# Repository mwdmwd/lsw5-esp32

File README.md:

# lsw5-esp32

> ESP32-based replacement PCB for the Deye/Sofar/Igen/Solarman/... LSW-5 *Stick Logger* with RS-485 CT meter emulation

This is a replacement ESP32-S3 daughterboard for the "LSW-5" *Stick Logger* (FCC ID [2A4FRLSW-5](https://fccid.io/2A4FRLSW-5)).

It replaces the original board, which is based on a [Hi-Flying HF-LPT270](http://www.hi-flying.com/hf-lpt270) [^lpt270] ([BL602](https://en.bouffalolab.com/product/?type=detail&id=1) inside[^lpt270-why-not]). With an ESP32-S3, it enables ESPHome support while keeping the *Stick Logger*'s modern, minimalistic appearance intact[^rs485-hole].

## Compatibility

* **Target Device**: LSW-5 *Stick Logger*, FCC ID: [2A4FRLSW-5](https://fccid.io/2A4FRLSW-5) and others (for example, mine, which does not have an FCC ID printed on it). May also fit the [2BC8DLSW-5](https://fccid.io/2BC8DLSW-5) (not verified, no internal photos), or other types of *Stick Logger*.
  * If your *Stick Logger* looks similar to the FCC photos, this board may fit regardless of whether the inverter-side connector is USB, DB-9, or the round 4-pin type.
* **Connection**: This board replaces the internal daughterboard connected via two (2x3, 2x5) socketed 2 mm pin headers.

## Features

* **ESP32-S3** (WROOM-1U-N16R8) with WiFi, BLE and a USB-C port for flashing/debugging.
* Works with **ESPHome**.
* 2.54 mm **expansion header** with 4 GPIOs with no predetermined function. Add a temperature sensor, I²C display, or any peripheral supported by ESPHome (or any other software you choose to run).
* **Open source hardware** designed in KiCad.
* Isolated **RS-485** transceiver for meter emulation.
  * Requires external 5V supply, as available from the *Meter-485* port in (some?) Deye hybrid inverters. Or use a phone charger to power it.[^rs485-isolation]
  * One isolated RS-485 port is present, but it could *potentially* be used for both meter emulation and BMS communication by connecting those to the same bus and configuring addresses appropriately; the Deye DSP firmware is hardcoded to use `1` for the "external CT" meter and `2` for the "Grid Tie Meter2" so these addresses are not available for BMS use. Unsure about address `0`.
    * You could definitely choose to use it *only* for BMS communication, with projects like [esphome-jk-bms](https://github.com/syssi/esphome-jk-bms)
* **LEDs**: on-board status LEDs (NET, RDY, COM) matching the translucent windows in the stock case mapped to ESP32 GPIOs.

## Hardware

The design files (schematics and PCB layout) are available in this repository.

### Pinout

| Function                               | ESP32 pin         | Location                      | Remarks                                                                     |
| :------------------------------------- | :---------------- | :---------------------------- | :-------------------------------------------------------------------------- |
| **3.3V input** from carrier board      | `3V3`             | J4 pins 5, 6                  |                                                                             |
| **GND** from carrier board             | `GND`             | J1 pins 1, 2, 3; J4 pins 9, 10 |                                                                             |
|                                        |                   |                               |                                                                             |
| **RX from inverter** (RS232 [^rs232])  | `GPIO16`          | J4 pin 8                      |                                                                             |
| **TX to inverter** (RS232)             | `GPIO17`          | J4 pin 7                      |                                                                             |
| **RX from RS485**                      | `GPIO21`          | onboard                       |                                                                             |
| **TX to RS485**                        | `GPIO48`          | onboard                       |                                                                             |
| **DE to RS485**                        | `GPIO47`          | onboard                       |                                                                             |
|                                        |                   |                               |                                                                             |
| **ESP32 boot mode**                    | `GPIO0`           | J1 pin 4                      | Connected to GND by the momentary switch on the bottom of the carrier board |
| **RX(?) from SIM card slot**           | `GPIO5`           | J4 pin 1                      | Slot is not populated on the carrier board, can use as GPIO                 |
| **TX(?) from SIM card slot**           | `GPIO4`           | J4 pin 4                      | Slot is not populated on the carrier board, can use as GPIO                 |
|                                        |                   |                               |                                                                             |
| **NET** LED                            | `GPIO40`          | onboard                       | Active low                                                                  |
| **COM** LED                            | `GPIO38`          | onboard                       | Active low                                                                  |
| **RDY** LED                            | `GPIO39`          | onboard                       | Active low                                                                  |
|                                        |                   |                               |                                                                             |
| **Programming port**[^usbc] 3.3V input | `3V3`             | J2 pin 1                      |                                                                             |
| **TX to external UART programmer**     | `TXD0` / `GPIO43` | J2 pin 2                      | Mind the startup messages                                                   |
| **RX from external UART programmer**   | `RXD0` / `GPIO44` | J2 pin 3                      |                                                                             |
| **GND**                                | `GND`             | J2 pin 4                      |                                                                             |
|                                        |                   |                               |                                                                             |
| **Expansion port:** 3.3V               | `3V3`             | J_EXP1 pin 1                  |                                                                             |
| Unassigned                             | `GPIO9`           | J_EXP1 pin 2                  |                                                                             |
| Unassigned                             | `GPIO10`          | J_EXP1 pin 3                  |                                                                             |
| Unassigned                             | `GPIO11`          | J_EXP1 pin 4                  |                                                                             |
| Unassigned                             | `GPIO12`          | J_EXP1 pin 5                  |                                                                             |
| GND                                    | `GND`             | J_EXP1 pin 6                  |                                                                             |
|                                        |                   |                               |                                                                             |
| **5V input** for RS485 transceiver     |                   | J6 pin 1                      |                                                                             |
| **GND** for RS485 transceiver          |                   | J6 pin 2                      |                                                                             |
| RS485 **A/+**                          |                   | J6 pin 3                      |                                                                             |
| RS485 **B/-**                          |                   | J6 pin 4                      |                                                                             |

There are two connections to the inverter:

- `GPIO16`/`GPIO17` connect to the inverter's MCU1/HMI through the logger port using the logger carrier's RS232 transceiver.
- `GPIO21`/`GPIO48`/`GPIO47` drive this board's RS485 transceiver and connect to the inverter's separate Meter-485 port, which is handled directly by MCU2/DSP.

## Errata

Board revisions refer to manufactured Gerber releases, tagged in Git as `p0`, `p1`, etc. The current KiCad files may already contain changes for the next unreleased revision; those changes are not listed here until a board is manufactured. For example, if the schematic says `p2` but there is no `p2` tag, that revision has not been manufactured yet.

Errata are listed by the newest affected revision. Older revisions also inherit the errata listed above them. For example, a `p0` board has both the `p1` and `p0` errata.

* `p1`
  * RS485 port: GND/5V labels swapped on silkscreen
  * Carrier board pin headers: silkscreen is on the wrong side
  * R5 should be 10 kΩ, not 100 kΩ
  * COM and NET LED labels swapped on silkscreen
  * LEDs are connected backwards compared to the intended design
  * RS485 bus interface includes series resistors, changed to 0 Ω at the moment, but either way they are not in a good place for proper termination (as the 120 Ω termination resistor is *after* the series resistor, not before), so they should probably be removed completely
* `p0`
  * No revision label on silkscreen
  * Non-isolated RS485 transceiver is used

## Firmware

[ESPHome](https://github.com/esphome/esphome), I suppose? This board is compatible with various existing ESPHome configurations (sometimes requiring minor adjustments).

* **[esphome-deye-inverter](https://github.com/Lewa-Reka/esphome-deye-inverter)**: A very comprehensive configuration for Deye inverters, including probably all of the sensors and switches you could ever want.
* **[esphome-for-deye](https://github.com/klatremis/esphome-for-deye)**: The classic.
* **[Sunsynk-Home-Assistant-Dash](https://github.com/slipx06/Sunsynk-Home-Assistant-Dash/tree/main/ESPHome%20Configs)**: You'll need to adjust the UART pins.
* *[your configuration here?]*

### Example configuration for board-specific features

A sample [`esphome/lsw5-esp32.yaml`](./esphome/lsw5-esp32.yaml) file is included in this repository. It serves as a starting point, illustrating the correct pin mappings for this specific board. It includes basic MQTT setup and RS-485 configuration for external meter emulation with source data over MQTT, as well as LED support.

> [!NOTE]
> The inverter polls the RS-485 meter every 125 ms, except every 10th attempt which is delayed by 125 ms as the inverter tries to write `float32(0.0)` to register 286 on device 0xab. I have not been able to identify the reason / meaning of this.
>
> You should aim to keep the data in your emulator as fresh as possible to minimize over/undershooting of the *Zero Export to Grid* feature under meter emulation.

## License

The hardware design files are licensed under the CERN Open Hardware Licence Version 2 - Strongly Reciprocal (CERN-OHL-S-2.0). See [LICENSES/CERN-OHL-S-2.0.txt](./LICENSES/CERN-OHL-S-2.0.txt) for details.

The example ESPHome configuration is based on an Apache-2.0-licensed configuration and has been modified for this project. It is distributed under the Apache License, Version 2.0. See [LICENSES/Apache-2.0.txt](./LICENSES/Apache-2.0.txt) and [esphome/NOTICE](./esphome/NOTICE) for details.

All other supporting files and tools are licensed under the GNU General Public License Version 3 or, at your option, any later version (GPL-3.0-or-later). See [LICENSES/GPL-3.0.txt](./LICENSES/GPL-3.0.txt) for details.

> [!CAUTION]
> Please be careful with electricity, always disconnect the *Stick Logger* from the inverter before replacing its internal board, always turn off the inverter and disconnect it from all power sources before (dis)connecting the *Stick Logger*, and so on. I will not be responsible if your warranty is voided, your inverter is damaged, or you get shocked. If you are not sure about something, ask for help from someone who is qualified to work with power electronics.

----------

[^lpt270]: https://fccid.io/2ACSVHF-LPT270-0F
[^rs485-hole]: unless you decide to cut a hole in the case to route out the Meter-485 cable. Or cut a bit of the plastic around the DB-9 plug out and route it there, but there is a risk of forgetting about the additional cable and causing damage when enthusiastically removing the *Stick Logger*. Or route it through the reset button hole.
[^rs485-isolation]: Added in `p1`, the story is that it would work fine until connecting the RS-485 (then all sorts of weird stuff would happen). I had seen some noise between the `GND`s in the RS-485 port and the RS-232 port, and the fact that they are not electrically connected, so I decided to make an isolated revision. Then it turned out that with 3cb155f6de7685bc65d782d9486902e5723dc495 my p0 board works on the bench, but isolation seems to be a good idea regardless.
[^rs232]: Through the RS232 transceiver on the carrier board inside the *Stick Logger* which this board plugs into.
[^usbc]: Recommended to use the USB-C port for programming instead
[^lpt270-why-not]: The ESP32-S3 was chosen because its software development experience and ESPHome support are substantially better.

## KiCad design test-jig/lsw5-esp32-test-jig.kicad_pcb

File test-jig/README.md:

# lsw5-esp32 test-jig

If you need this, you will know how to use it.

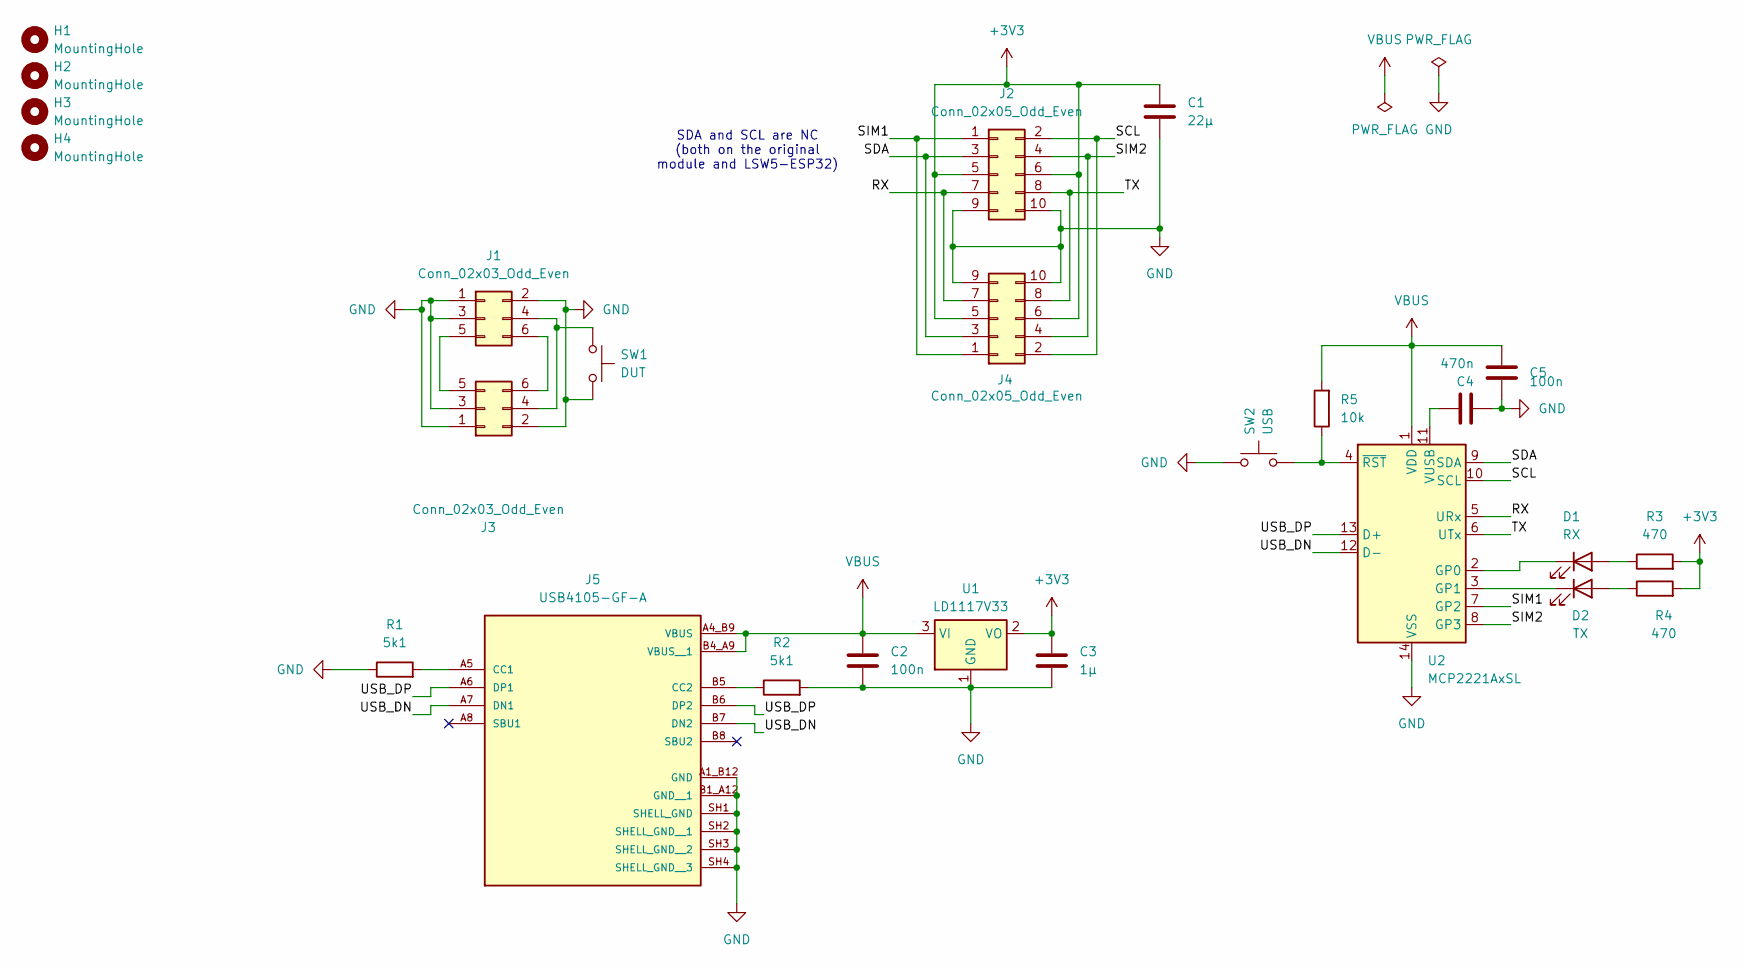
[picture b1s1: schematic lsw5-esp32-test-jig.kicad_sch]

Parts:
C1: 22μ; C_0805_2012Metric_Pad1.18x1.45mm_HandSolder
C2, C5: 100n; C_0603_1608Metric_Pad1.08x0.95mm_HandSolder
C3: 1μ; C_0603_1608Metric_Pad1.08x0.95mm_HandSolder
C4: 470n; C_0603_1608Metric_Pad1.08x0.95mm_HandSolder
D1: RX; LED_0603_1608Metric_Pad1.05x0.95mm_HandSolder
D2: TX; LED_0603_1608Metric_Pad1.05x0.95mm_HandSolder
H1, H2, H3, H4: MountingHole; MountingHole_3.2mm_M3
J1: Conn_02x03_Odd_Even; PinSocket_2x03_P2.00mm_Vertical
J2: Conn_02x05_Odd_Even; PinSocket_2x05_P2.00mm_Vertical
J3: Conn_02x03_Odd_Even; PinHeader_2x03_P2.54mm_Vertical
J4: Conn_02x05_Odd_Even; PinHeader_2x05_P2.54mm_Vertical
J5: USB4105-GF-A; GCT_USB4105-GF-A; PARTREV B4
R1, R2: 5k1; R_0603_1608Metric_Pad0.98x0.95mm_HandSolder
R3, R4: 470; R_0603_1608Metric_Pad0.98x0.95mm_HandSolder
R5: 10k; R_0603_1608Metric_Pad0.98x0.95mm_HandSolder
SW1: DUT; SW_PUSH_6mm
SW2: USB; SW_PUSH_6mm
U1: LD1117V33; TO-220-3_Vertical
U2: MCP2221AxSL; SOIC-14_3.9x8.7mm_P1.27mm

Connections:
+3V3: C1.1, C3.1, J2.5, J2.6, J4.5, J4.6, R3.2, R4.2, U1.2 (VO)
/RX: J2.7, J4.7, U2.5 (URx)
/SCL: J2.2, J4.2, U2.10 (SCL)
/SDA: J2.3, J4.3, U2.9 (SDA)
/SIM1: J2.1, J4.1, U2.7 (GP2)
/SIM2: J2.4, J4.4, U2.8 (GP3)
/TX: J2.8, J4.8, U2.6 (UTx)
/USB_DN: J5.A7 (DN1), J5.B7 (DN2), U2.12 (D-)
/USB_DP: J5.A6 (DP1), J5.B6 (DP2), U2.13 (D+)
GND: C1.2, C2.2, C3.2, C4.2, C5.2, J1.1, J1.2, J1.3, J2.9, J2.10, J3.1, J3.2, J3.3, J4.9, J4.10, J5.A1_B12 (GND), J5.B1_A12 (GND__1), J5.SH1 (SHELL_GND), J5.SH2 (SHELL_GND__1), J5.SH3 (SHELL_GND__2), J5.SH4 (SHELL_GND__3), R1.1, R2.2, SW1.2, SW2.1, U1.1 (GND), U2.14 (VSS)
unnamed: D1.2 (A), R3.1
unnamed: D1.1 (K), U2.2 (GP0)
unnamed: D2.2 (A), R4.1
unnamed: D2.1 (K), U2.3 (GP1)
unnamed: J1.4, J3.4, SW1.1
unnamed: J1.5, J3.5
unnamed: J1.6, J3.6
unnamed: J5.A5 (CC1), R1.2
unnamed: J5.B5 (CC2), R2.1
unnamed: C4.1, U2.11 (VUSB)
unnamed: R5.1, SW2.2, U2.4 (~RST)
VBUS: C2.1, C5.1, J5.A4_B9 (VBUS), J5.B4_A9 (VBUS__1), R5.2, U1.3 (VI), U2.1 (VDD)

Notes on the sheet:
SDA and SCL are NC (both on the original module and LSW5-ESP32)

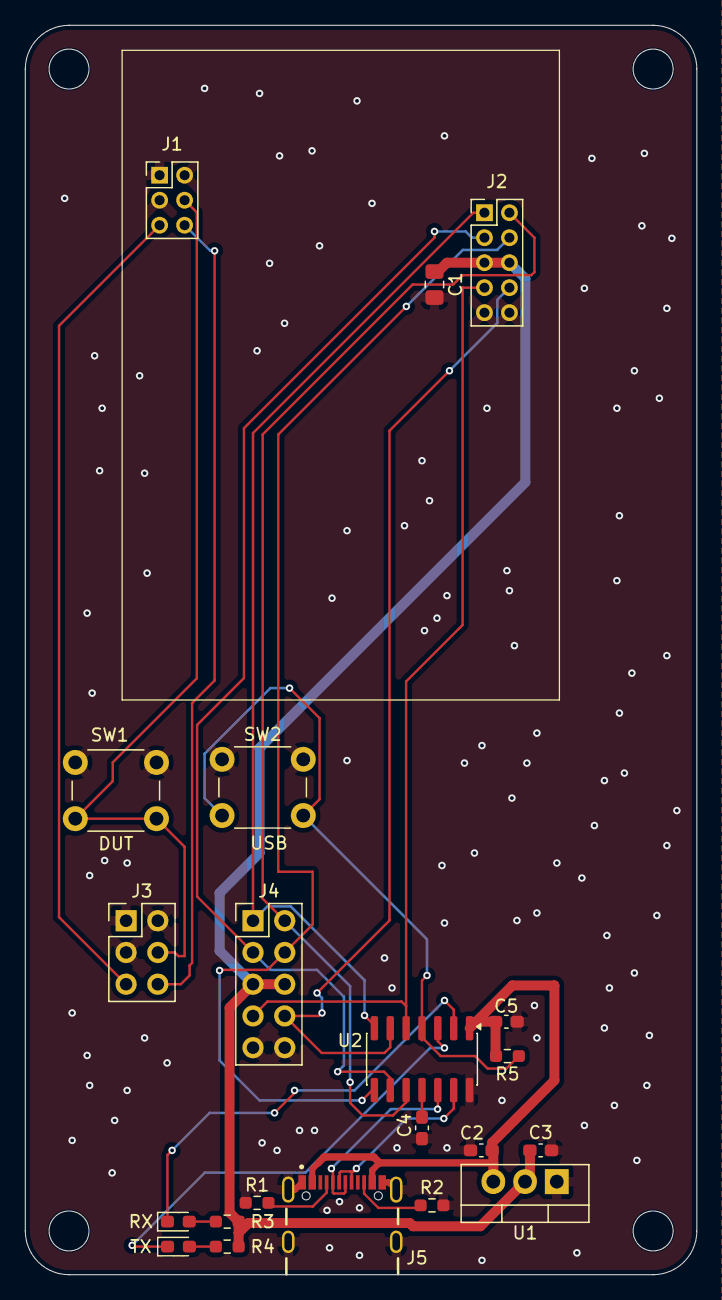
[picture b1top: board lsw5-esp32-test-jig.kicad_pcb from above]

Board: 2 copper layers, 53.8 x 100.0 mm, 25 parts (0 on the bottom side), 22 nets.

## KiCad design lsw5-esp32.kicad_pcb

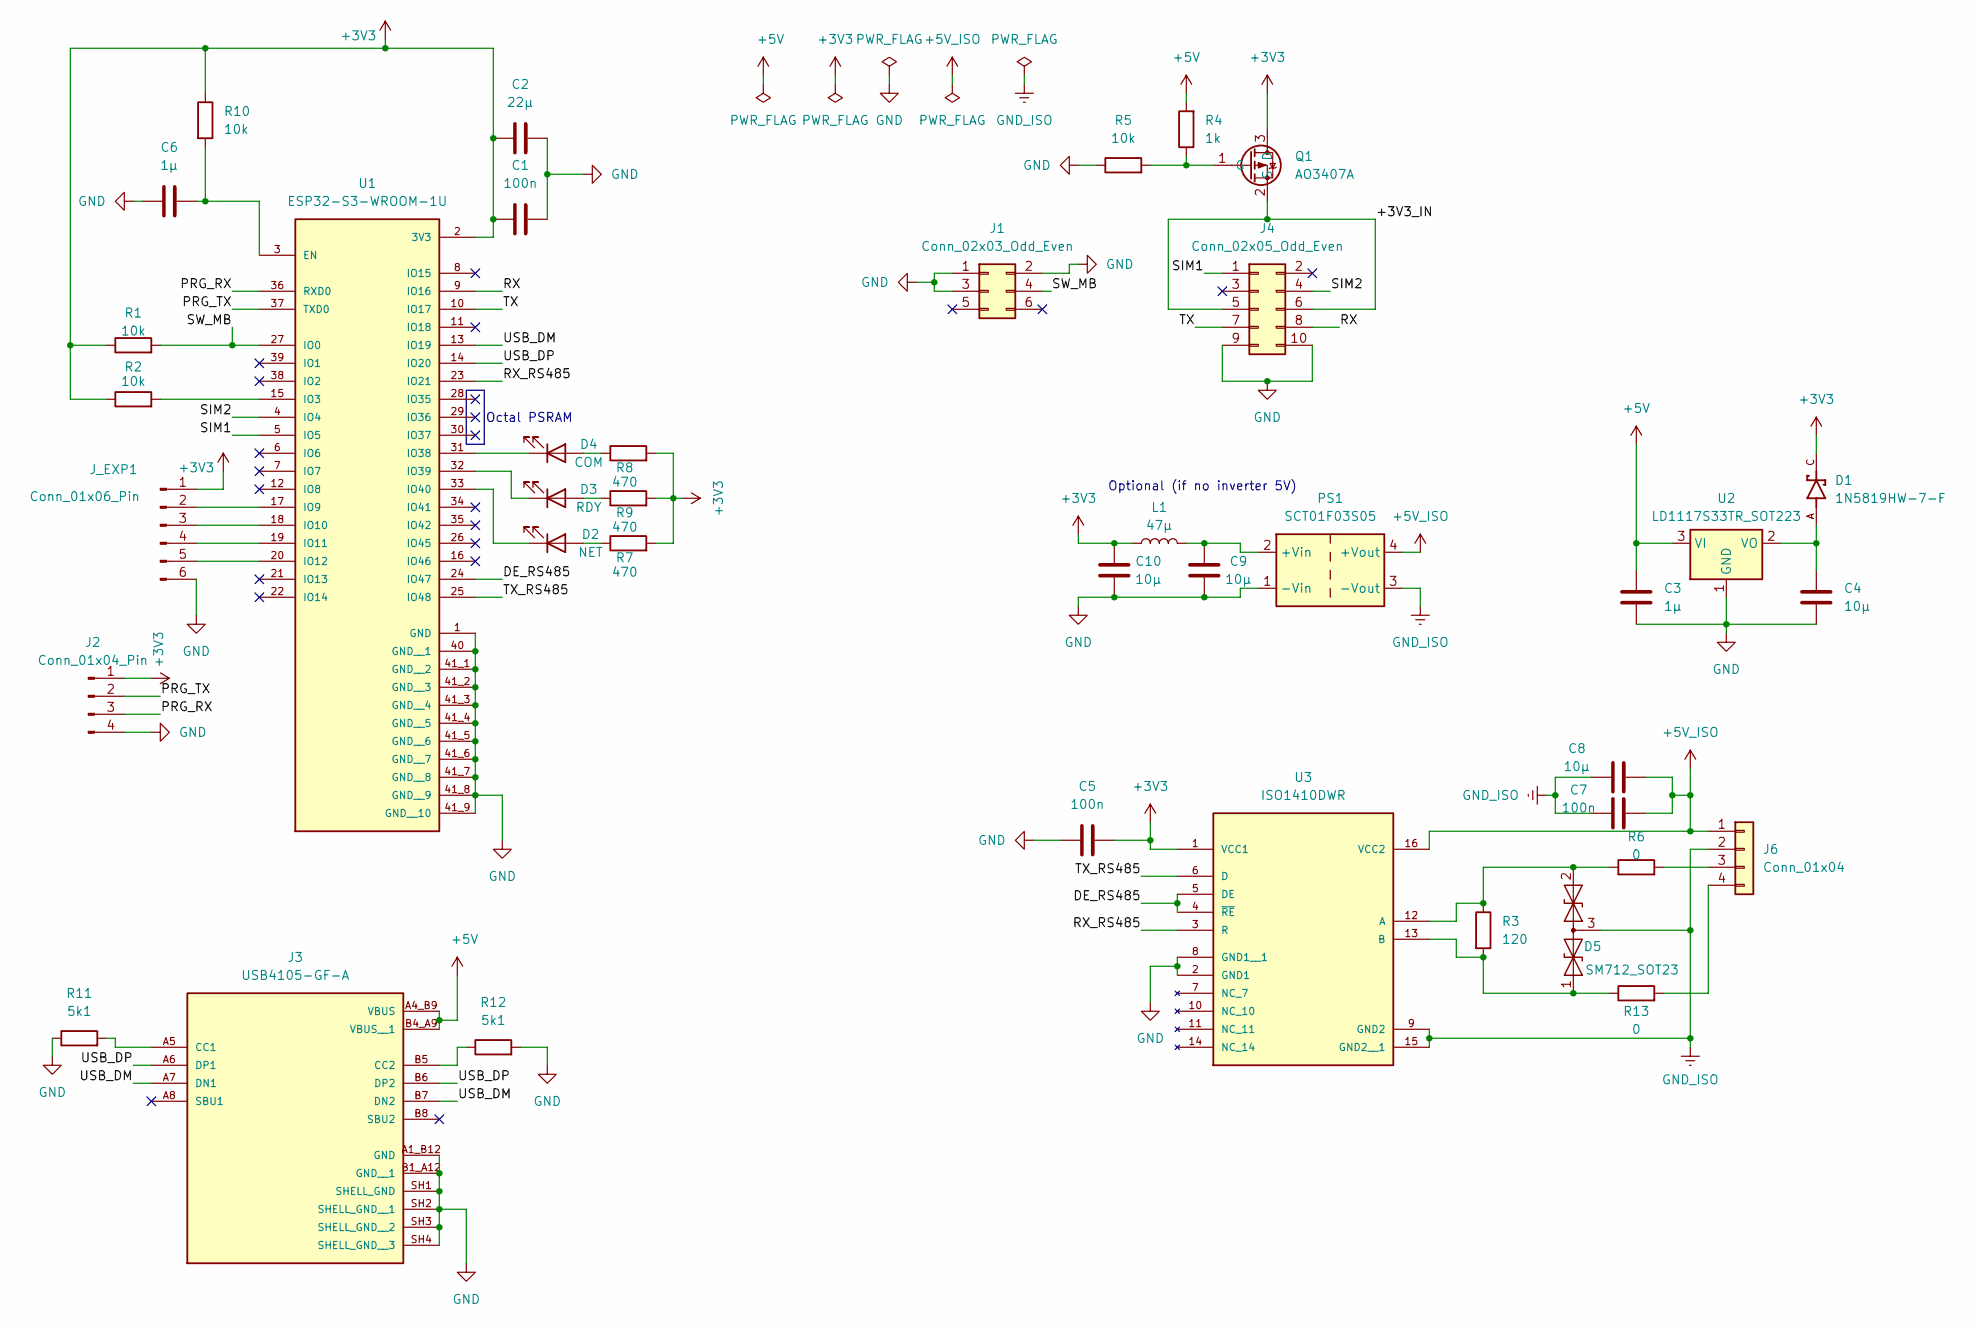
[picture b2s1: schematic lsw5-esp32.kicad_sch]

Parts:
C1, C5, C7: 100n; C_0603_1608Metric_Pad1.08x0.95mm_HandSolder
C2: 22μ; C_0805_2012Metric_Pad1.18x1.45mm_HandSolder
C3, C6: 1μ; C_0603_1608Metric_Pad1.08x0.95mm_HandSolder
C4, C8, C9, C10: 10μ; C_0805_2012Metric_Pad1.18x1.45mm_HandSolder
D1: 1N5819HW-7-F; SOD3715X145N; PARTREV 18-2
D2: NET; LED_0603_1608Metric_Pad1.05x0.95mm_HandSolder
D3: RDY; LED_0603_1608Metric_Pad1.05x0.95mm_HandSolder
D4: COM; LED_0603_1608Metric_Pad1.05x0.95mm_HandSolder
D5: SM712_SOT23; SOT-23
J1: Conn_02x03_Odd_Even; PinHeader_2x03_P2.00mm_Vertical
J2: Conn_01x04_Pin; PinHeader_1x04_P2.54mm_Vertical
J3: USB4105-GF-A; GCT_USB4105-GF-A; PARTREV B4
J4: Conn_02x05_Odd_Even; PinHeader_2x05_P2.00mm_Vertical
J6: Conn_01x04; PinHeader_1x04_P2.54mm_Vertical
J_EXP1: Conn_01x06_Pin; PinHeader_1x06_P2.54mm_Horizontal
L1: 47μ; L_Ferrocore_DJNR-4018
PS1: SCT01F03S05; Converter_DCDC_Murata_MEE1SxxxxSC_THT
Q1: AO3407A; SOT-23
R1, R2, R5, R10: 10k; R_0603_1608Metric_Pad0.98x0.95mm_HandSolder
R3: 120; R_0603_1608Metric_Pad0.98x0.95mm_HandSolder
R4: 1k; R_0603_1608Metric_Pad0.98x0.95mm_HandSolder
R6, R13: 0; R_0603_1608Metric_Pad0.98x0.95mm_HandSolder
R7, R8, R9: 470; R_0603_1608Metric_Pad0.98x0.95mm_HandSolder
R11, R12: 5k1; R_0603_1608Metric_Pad0.98x0.95mm_HandSolder
U1: ESP32-S3-WROOM-1U; ESP32-S3-WROOM-1U-N16R8; PARTREV v1.1
U2: LD1117S33TR_SOT223; SOT-223-3_TabPin2
U3: ISO1410DWR; SOIC127P1030X265-16N; PARTREV H

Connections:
+3V3: C1.1, C2.1, C5.1, C10.2, D1.C, J2.1, J_EXP1.1, L1.1, Q1.3 (D), R1.1, R2.1, R7.2, R8.2, R9.2, R10.1, U1.2 (3V3), U3.1 (VCC1)
+5V: C3.2, J3.A4_B9 (VBUS), J3.B4_A9 (VBUS__1), R4.2, U2.3 (VI)
+5V_ISO: C7.1, C8.1, J6.1, PS1.4 (+Vout), U3.16 (VCC2)
/+3V3_IN: J4.5, J4.6, Q1.2 (S)
/DE_RS485: U1.24 (IO47), U3.4 (~RE), U3.5 (DE)
/PRG_RX: J2.3, U1.36 (RXD0)
/PRG_TX: J2.2, U1.37 (TXD0)
/RX: J4.8, U1.9 (IO16)
/RX_RS485: U1.23 (IO21), U3.3 (R)
/SIM1: J4.1, U1.5 (IO5)
/SIM2: J4.4, U1.4 (IO4)
/SW_MB: J1.4, R1.2, U1.27 (IO0)
/TX: J4.7, U1.10 (IO17)
/TX_RS485: U1.25 (IO48), U3.6 (D)
/USB_DM: J3.A7 (DN1), J3.B7 (DN2), U1.13 (IO19)
/USB_DP: J3.A6 (DP1), J3.B6 (DP2), U1.14 (IO20)
GND: C1.2, C2.2, C3.1, C4.1, C5.2, C6.1, C9.1, C10.1, J1.1, J1.2, J1.3, J2.4, J3.A1_B12 (GND), J3.B1_A12 (GND__1), J3.SH1 (SHELL_GND), J3.SH2 (SHELL_GND__1), J3.SH3 (SHELL_GND__2), J3.SH4 (SHELL_GND__3), J4.9, J4.10, J_EXP1.6, PS1.1 (-Vin), R5.1, R11.1, R12.2, U1.1 (GND), U1.40 (GND__1), U1.41_1 (GND__2), U1.41_2 (GND__3), U1.41_3 (GND__4), U1.41_4 (GND__5), U1.41_5 (GND__6), U1.41_6 (GND__7), U1.41_7 (GND__8), U1.41_8 (GND__9), U1.41_9 (GND__10), U2.1 (GND), U3.2 (GND1), U3.8 (GND1__1)
GND_ISO: C7.2, C8.2, D5.3 (common), J6.2, PS1.3 (-Vout), U3.9 (GND2), U3.15 (GND2__1)
unnamed: C9.2, L1.2, PS1.2 (+Vin)
unnamed: D2.2 (A), R7.1
unnamed: D2.1 (K), U1.33 (IO40)
unnamed: D3.2 (A), R9.1
unnamed: D3.1 (K), U1.32 (IO39)
unnamed: D4.2 (A), R8.1
unnamed: D4.1 (K), U1.31 (IO38)
unnamed: D5.1 (A1), R3.2, R13.1, U3.13 (B)
unnamed: D5.2 (A2), R3.1, R6.1, U3.12 (A)
unnamed: J3.A5 (CC1), R11.2
unnamed: J3.B5 (CC2), R12.1
unnamed: J6.3, R6.2
unnamed: J6.4, R13.2
unnamed: J_EXP1.2, U1.17 (IO9)
unnamed: J_EXP1.3, U1.18 (IO10)
unnamed: J_EXP1.4, U1.19 (IO11)
unnamed: J_EXP1.5, U1.20 (IO12)
unnamed: Q1.1 (G), R4.1, R5.2
unnamed: C6.2, R10.2, U1.3 (EN)
unnamed: R2.2, U1.15 (IO3)
unnamed: C4.2, D1.A, U2.2 (VO)

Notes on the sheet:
Optional (if no inverter 5V)
Octal PSRAM

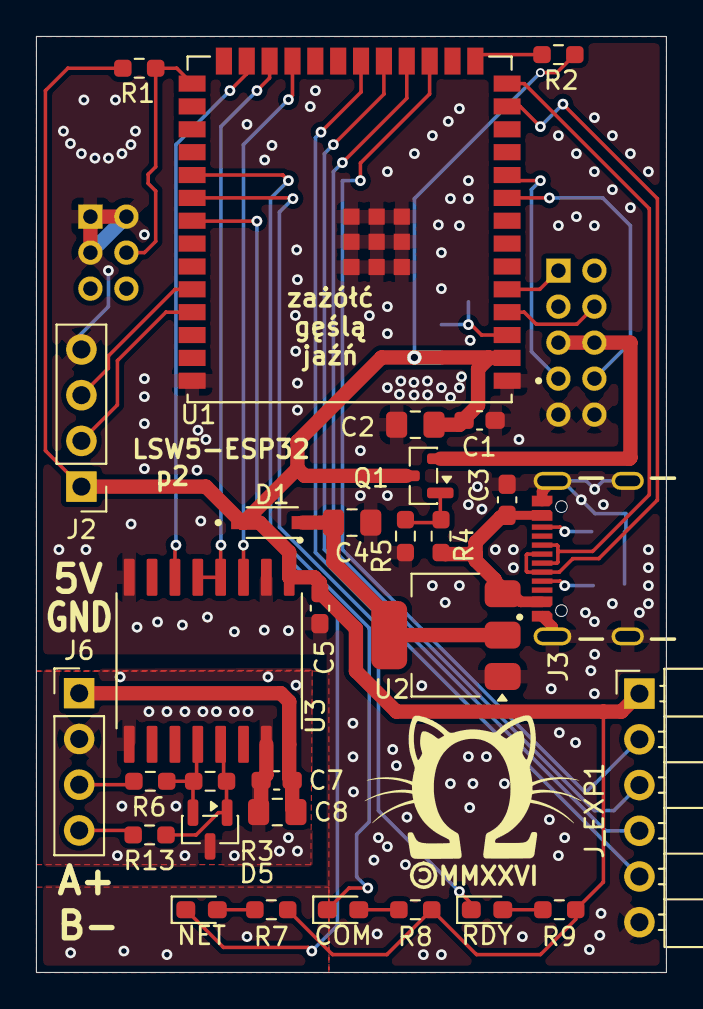
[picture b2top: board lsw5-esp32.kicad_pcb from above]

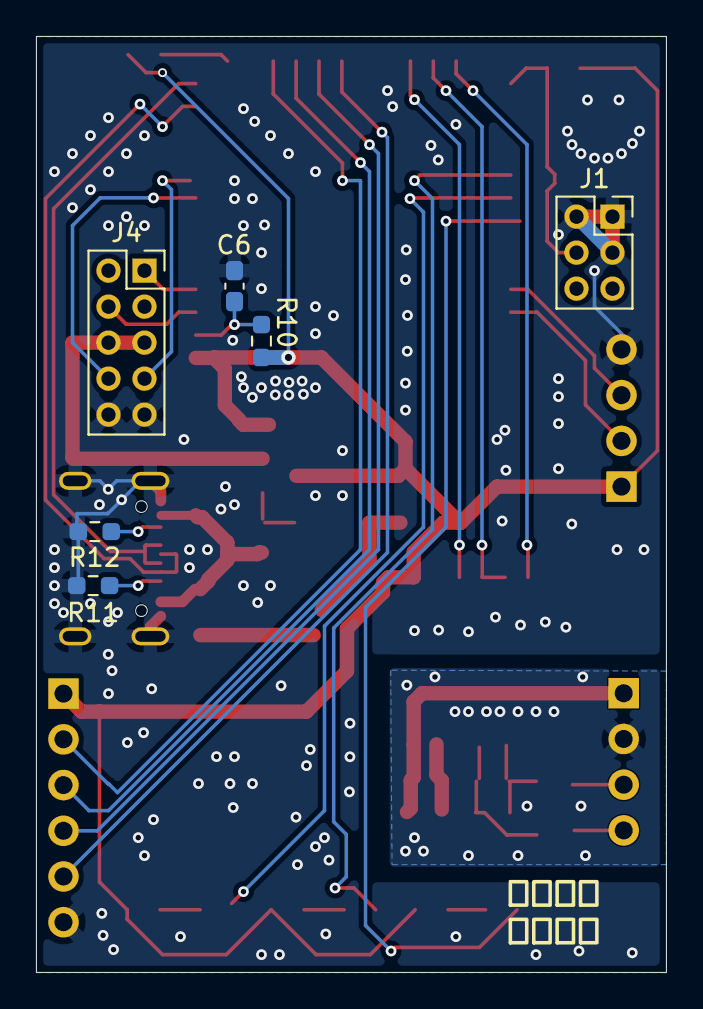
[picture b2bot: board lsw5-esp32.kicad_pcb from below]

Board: 2 copper layers, 35.0 x 52.0 mm, 36 parts (6 on the bottom side), 38 nets.

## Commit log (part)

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2025-12-27 init
2025-12-27 add shipped p0
2025-12-27 increase a few clearances
2026-05-03 Move RS485 transceiver off octal SPI pins
2026-05-03 improve noise immunity of power switch
2026-05-03 remove net name labels
2026-05-03 test jig: Update button labels on schematic
2026-05-03 Set 3D models
2026-05-03 add shipped p1
2026-05-03 set title and revision
2026-05-03 Add p1 label
2026-05-03 Fix swapped LED labels
2026-05-03 test jig: fix 2mm headers pin 1 silkscreen
2026-05-03 Fix pin header footprint being on the wrong side, not that it matters for THT but to have a reasonable render
2026-05-03 add test jig
2026-05-03 p1 isolate RS485 transceiver
2026-05-03 Fix fp path, centralise PWR_FLAG
2026-05-03 Fix DRC for 2 layer
2026-05-04 Add fake-inverter
2026-05-04 add yaml
2026-05-04 Fix LED labels on silkscreen
2026-05-04 Fix swapped 5V/GND silkscreen on RS485 port
2026-05-04 test jig: Fix USB only working on one side
2026-05-04 RS485 series resistors to 0Ω
    To be removed in p2? Also, putting the series resistors before the 120Ω
    termination is bad, not that any of these considerations *probably*
    matter for chassis wiring
2026-05-04 batt remove unneeded
2026-05-04 pycache
2026-05-04 remove dc tmperature (always shows 25 °C)
2026-05-04 Add battery
2026-05-04 Fix backwards LED (aka silkscreen)
2026-05-04 yaml add sensors
2026-05-04 rename to inverter
2026-05-04 discovery for every sensor
2026-05-04 test jig: Fix MCP2221A V_USB capacitor value
    DS20005565E-page 17
    > The VUSB pin requires an external bypass capacitor
    > with a value between 0.22 and 0.47 μF (ceramic cap)
2026-05-04 remove discovery false
2026-05-04 ignore KiCad history
2026-05-04 Add force off grid switch
2026-05-04 prevent spike on energy readout if generator sensor is not updated yet
2026-05-04 Add documentation
2026-05-04 add state classes
2026-05-04 Heap size → KiB
2026-05-04 yaml
2026-05-04 remove Battery Corrected Capacity
2026-05-04 filter out 0 on PV production
2026-05-04 add internal CT power
2026-05-04 filter out 0 temperatures
2026-05-04 add wifi signal
2026-05-04 subtract generator production from PV production
2026-05-04 Add load energy
2026-05-04 solar production offset -> substitution
2026-05-04 add battery current limits
2026-05-11 Add register notes
2026-05-11 format
2026-05-11 add render setup
2026-05-11 esphome fixes
2026-05-11 exclude 2.54 mm pin headers from pos
2026-05-12 upgrade to KiCad 10 format
2026-05-12 fix some missed warnings
2026-06-07 raise reboot timeout
2026-06-07 disable WiFi PSM
2026-06-07 fix inverter production generator offset
2026-06-22 out with server_registers in with modbus_server
    See https://www.github.com/esphome/esphome/commit/52e8c50f45a035362d62a1d47e967240ec6b65f6
2026-06-25 Actually fix Total PV Production going down when Total Generator Production updates
